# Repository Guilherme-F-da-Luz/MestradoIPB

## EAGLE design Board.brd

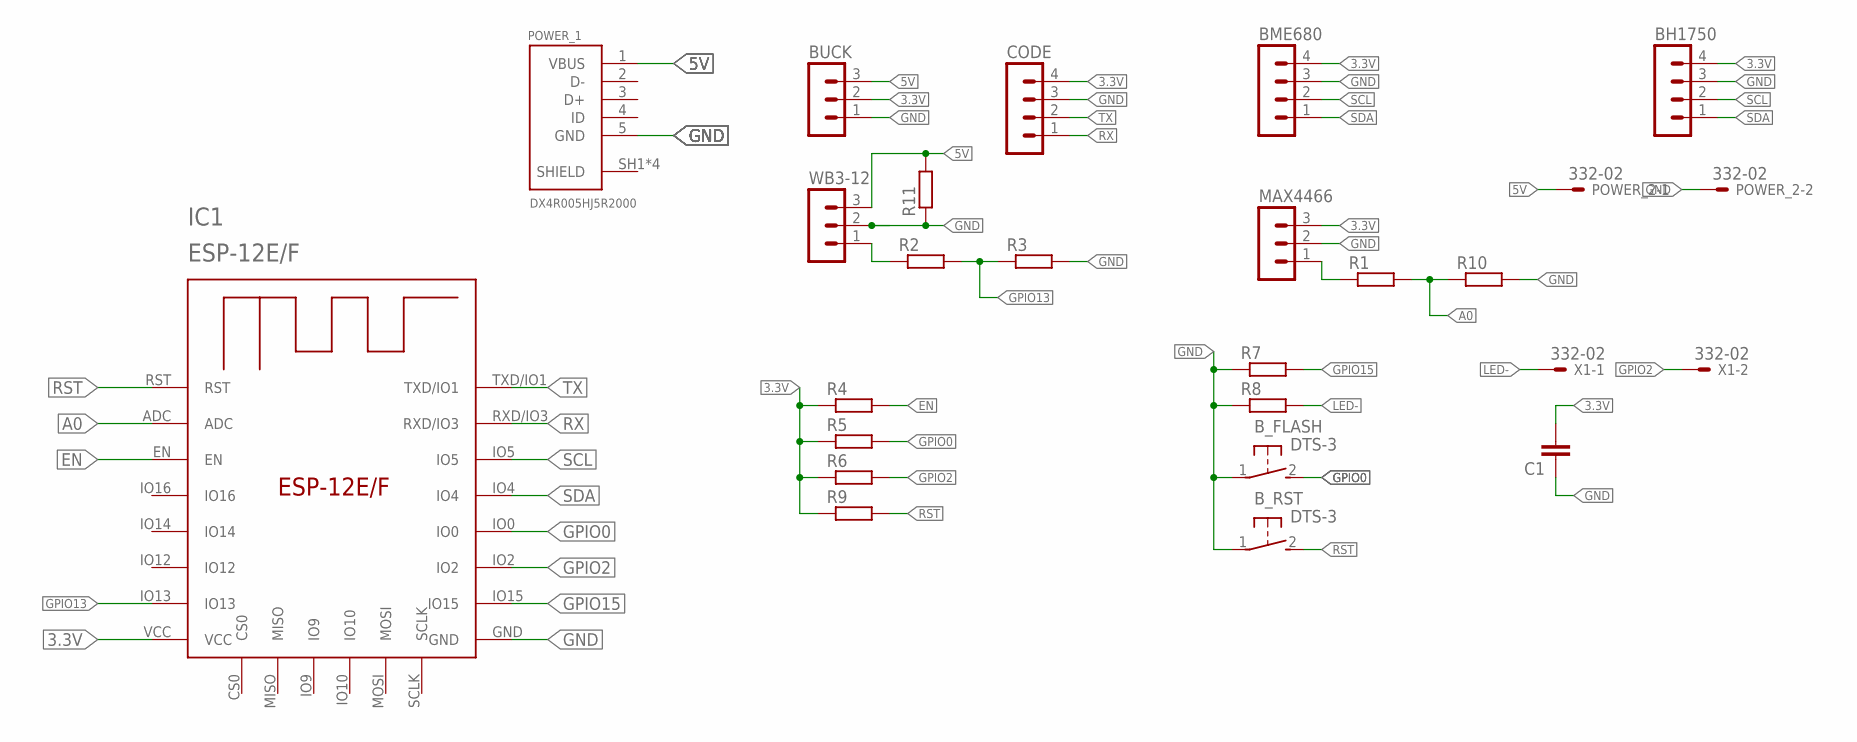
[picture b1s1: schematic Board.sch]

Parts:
BH1750: MA04-1
BME680: MA04-1
BUCK: MA03-1
B_FLASH: DTS-3
B_RST: DTS-3
C1: C-EU025-024X044; C025-024X044
CODE: MA04-1
IC1: ESP-12E/F; ESP-12E
MAX4466: MA03-1
POWER_1: DX4R005HJ5R2000
POWER_2: 332-02
R1, R2, R3, R4, R5, R6, R7, R8, R9, R10, R11: R-EU_0207/10; 0207/10
WB3-12: MA03-1
X1: 332-02

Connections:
3.3V: BH1750.4, BME680.4, BUCK.2, C1.2, CODE.4, IC1.VCC, MAX4466.3, R4.1, R5.1, R6.1, R9.1
5V: BUCK.3, POWER_1.1 (VBUS), POWER_2.1, R11.2, WB3-12.3
A0: IC1.ADC, R1.2, R10.1
EN: IC1.EN, R4.2
GND: BH1750.3, BME680.3, BUCK.1, B_FLASH.1, B_RST.1, C1.1, CODE.3, IC1.GND, MAX4466.2, POWER_1.5 (GND), POWER_2.2, R3.2, R7.1, R8.1, R10.2, R11.1, WB3-12.2
GPIO0: B_FLASH.2, IC1.IO0, R5.2
GPIO2: IC1.IO2, R6.2, X1.2
GPIO13: IC1.IO13, R2.2, R3.1
GPIO15: IC1.IO15, R7.2
LED-: R8.2, X1.1
unnamed: MAX4466.1, R1.1
unnamed: R2.1, WB3-12.1
RST: B_RST.2, IC1.RST, R9.2
RX: CODE.1, IC1.RXD/IO3
SCL: BH1750.2, BME680.2, IC1.IO5
SDA: BH1750.1, BME680.1, IC1.IO4
SHIELD: POWER_1.SH1 (SHIELD), POWER_1.SH2 (SHIELD), POWER_1.SH3 (SHIELD), POWER_1.SH4 (SHIELD)
TX: CODE.2, IC1.TXD/IO1

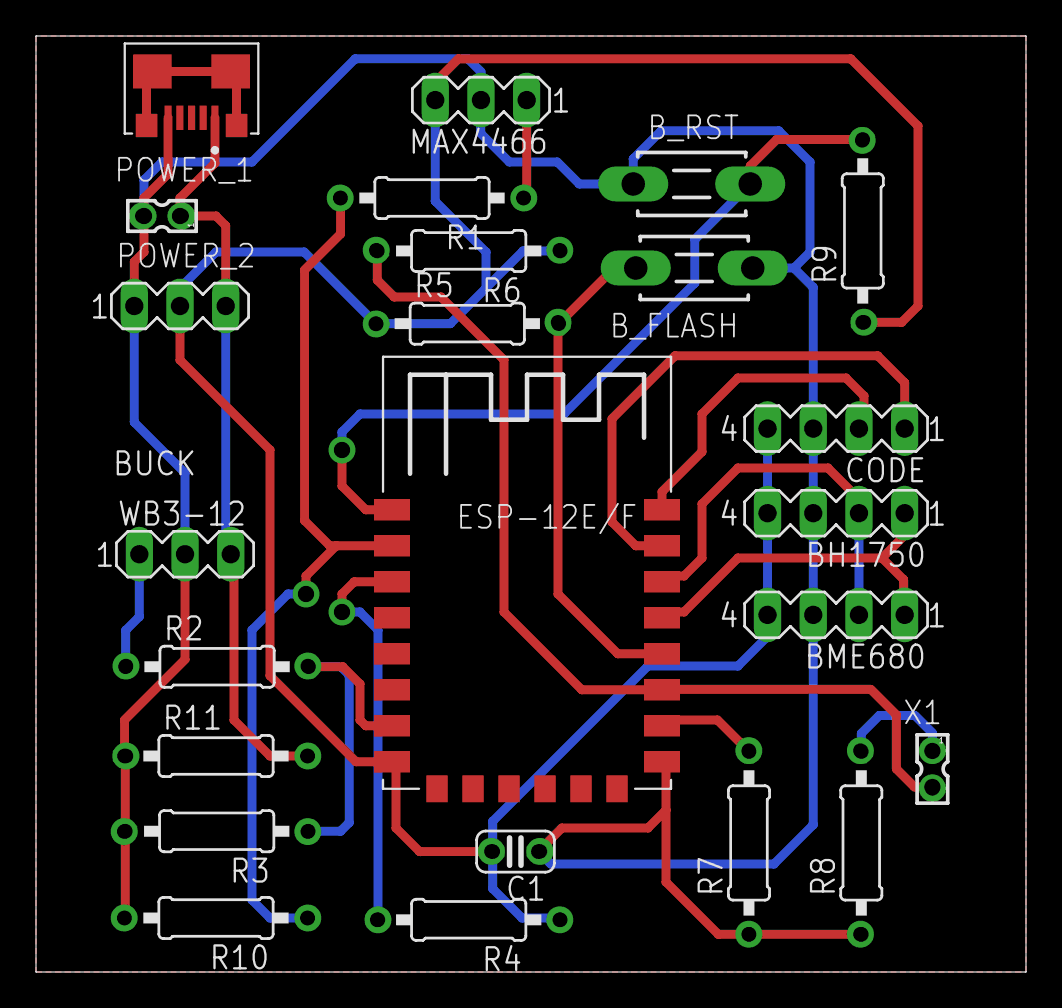
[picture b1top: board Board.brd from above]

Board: 2 copper layers, 55.0 x 52.0 mm, 24 parts (0 on the bottom side), 18 nets.
